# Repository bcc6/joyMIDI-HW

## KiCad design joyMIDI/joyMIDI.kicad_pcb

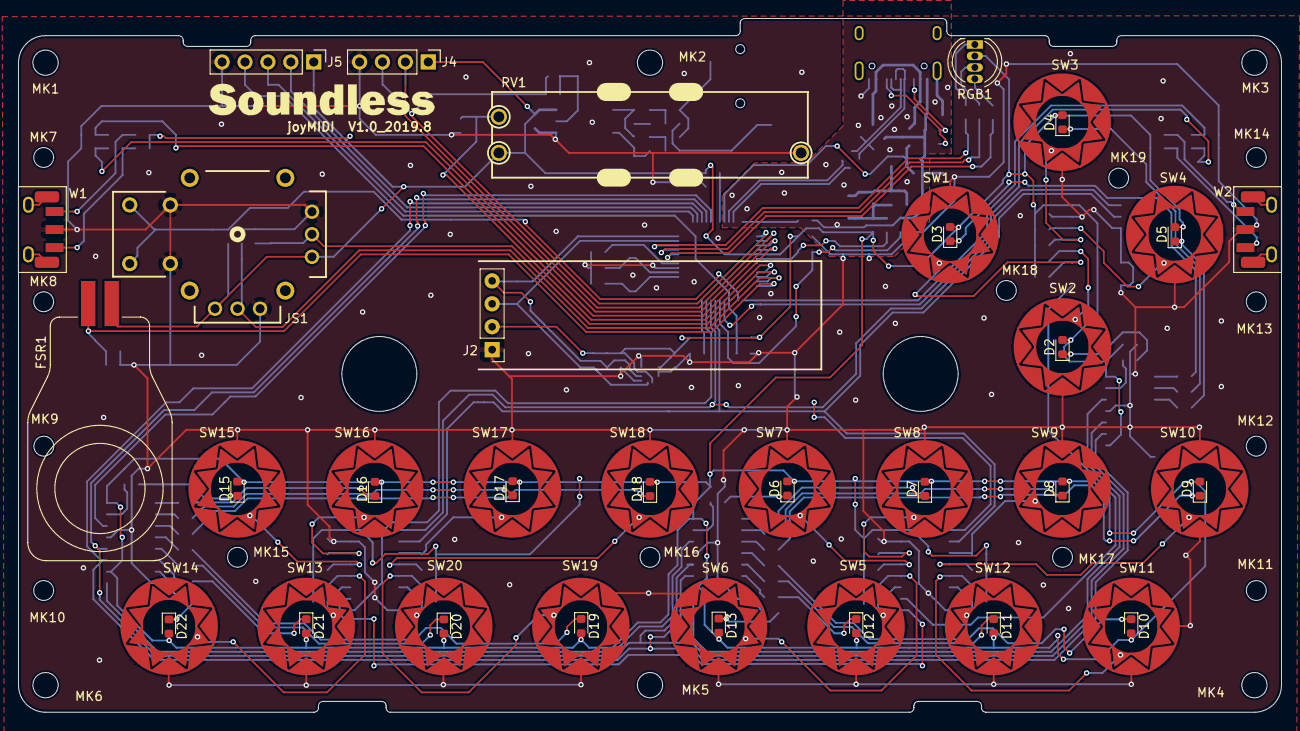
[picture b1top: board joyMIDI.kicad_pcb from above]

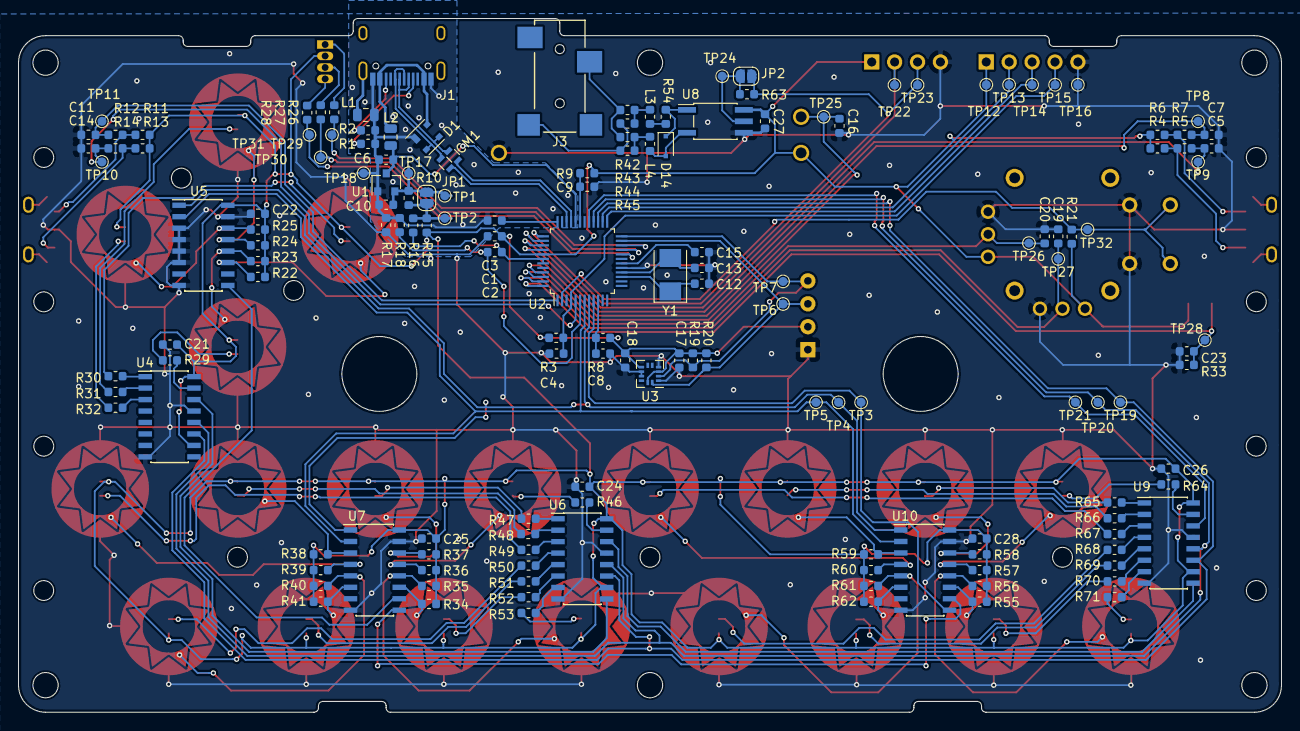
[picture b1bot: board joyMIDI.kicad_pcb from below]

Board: 2 copper layers, 140.0 x 76.9 mm, 221 parts (153 on the bottom side), 126 nets.

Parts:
C1, C2, C8, C9, C17, C18, C21, C22, C24, C25, C26, C27, C28: 100n; C_0603_1608Metric
C3, C4, C15: 1u; C_0603_1608Metric
C5, C7, C11, C14: 10n; C_0603_1608Metric
C6, C10: 4.7u; C_0603_1608Metric
C12, C13: 20p; C_0603_1608Metric
C16, C19, C20, C23: 1n; C_0603_1608Metric
CM1: 90R@100MHz; CommonChoke_Dual0603
D1: PRTR5V0U2X; PRTR5V0U2X_SOT-143B
D2, D3, D4, D5, D6, D7, D8, D9, D10, D11, D12, D13, D15, D16, D17, D18, D19, D20, D21, D22: LED; LED_0603_1608Metric
D14: 1N4148WS; D_SOD-323F
FSR1: GD10-20N; FSR_GD10-20N
J1: USB_Type_C_16P; HRO_TYPE-C-31-M-12
J2: HDR_01X04; Pin_Header_Straight_1x04_Pitch2.54mm_SmallHole
J3: AUDIO_JACK_TRS_4P_2.5mm; AUDIO_JACK_2.5mm_SJ-2524-SMT
J4: HDR_01X04; PinHeader_1x04_P2.54mm_Vertical
J5: HDR_01X05; PinHeader_1x05_P2.54mm_Vertical
JP1, JP2: SolderJumper; SolderJumper-2_P1.3mm_Open_RoundedPad1.0x1.5mm
JS1: Joystick; Joystick_FJM10K-S
L1: L0805/NC; L_0805_2012Metric
L2: L0805/600R_1A; L_0805_2012Metric
L3, L4: MMZ1608Y102BT; L_0603_1608Metric
MK1, MK2, MK3, MK4, MK5, MK6: NPTH_M2.6; NPTH_2.8mm_M2.6
MK7, MK8, MK9, MK10, MK11, MK12, MK13, MK14, MK15, MK16, MK17, MK18, MK19: NPTH_M2; NPTH_2.2mm_M2
R1, R2: 5.1K; R_0603_1608Metric
R3, R4, R5, R6, R7, R11, R12, R13, R14, R21, R22, R23, R24, R25, R34, R35, R36, R37, R38, R39, R40, R41, R55, R56, R57, R58, R59, R60, R61, R62: 10K; R_0603_1608Metric
R8, R9, R10, R15, R16, R17, R18, R42, R45, R63: 0R; R_0603_1608Metric
R19, R20: 4.7K; R_0603_1608Metric
R26, R27, R28, R54: 220; R_0603_1608Metric
R29, R30, R31, R32, R46, R47, R48, R49, R50, R51, R52, R53, R64, R65, R66, R67, R68, R69, R70, R71: 1K; R_0603_1608Metric
R33: 3.3K; R_0603_1608Metric
R43, R44: NC; R_0603_1608Metric
RGB1: LED_RGB_CA; LED_D4.8mm-4
RV1: VR_Slide; VR_Slide_F2031-NN
SW1, SW2, SW3, SW4, SW5, SW6, SW7, SW8, SW9, SW10, SW11, SW12, SW13, SW14, SW15, SW16, SW17, SW18, SW19, SW20: SW; RubberPad
TP1, TP2, TP3, TP4, TP5, TP6, TP7, TP8, TP9, TP10, TP11, TP12, TP13, TP14, TP15, TP16, TP17, TP18, TP19, TP20, TP21, TP22, TP23, TP24, TP25, TP26, TP27, TP28, TP29, TP30, TP31, TP32: TestPoint; TestPoint_Pad_D1.0mm
U1: AIC1746-33; SOT-23
U2: M452LE6AE; LQFP-48_7x7mm_P0.5mm
U3: BMA2xx; BMA2xx_LGA-12
U4, U6, U9: 74HC595; SOIC-16_3.9x9.9mm_P1.27mm
U5, U7, U10: 74HC165; SOIC-16_3.9x9.9mm_P1.27mm
U8: TLP2361; SO-5_4.4x3.6mm_P1.27mm
W1, W2: EC05E; EC05E1220202
Y1: 12M; Crystal_SMD_5032-2Pin_5.0x3.2mm

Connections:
/ADC1: C16.1, RV1.2, TP25.1, U2.45
/ADC2: C20.1, JS1.5, TP26.1, U2.46
/ADC3: C19.1, JS1.2, TP27.1, U2.47
/ADC4: C23.1, FSR1.1, R33.2, TP28.1, U2.48
/CURRENT_B: JP1.2, R10.1, R15.2, R16.2, TP2.1
/D+: CM1.4, D1.2, J1.A6, J1.B6
/D-: CM1.1, D1.3, J1.A7, J1.B7
/I2C_SCL: J2.3, R20.2, TP6.1, U2.23, U3.12
/I2C_SDA: J2.4, R19.2, TP7.1, U2.24, U3.2
/ICECLK: J5.3, TP14.1, U2.25
/ICEDAT: J5.2, TP13.1, U2.26
/JOG_1A: C7.1, R7.1, TP8.1, U2.40
/JOG_1B: C5.1, R5.1, TP9.1, U2.39
/JOG_2A: C14.1, R14.1, TP10.1, U2.5
/JOG_2B: C11.1, R12.1, TP11.1, U2.1
/KEY_CK: TP5.1, U2.7, U5.2, U7.2, U10.2
/KEY_ISP: JS1.7, R21.1, TP32.1, U2.2
/KEY_PL: TP4.1, U2.8, U5.1, U7.1, U10.1
/KEY_SI: TP3.1, U2.9, U10.9
/LED_B: R28.2, TP31.1, U2.20
/LED_DATA: TP21.1, U2.29, U9.14
/LED_G: R27.2, TP30.1, U2.21
/LED_R: R26.2, TP29.1, U2.22
/LED_RCLK: TP20.1, U2.28, U4.12, U6.12, U9.12
/LED_SRCLK: TP19.1, U2.27, U4.11, U6.11, U9.11
/MIDI_IN: JP2.1, R63.1, TP24.1, U8.5
/UART_RX: J4.3, JP2.2, R63.2, TP23.1, U2.37
/UART_TX: J4.2, TP22.1, U2.38
/VBAT: C8.1, R8.2, U2.10
/VDDIO: C9.1, R9.1, U2.31
/nRST: C4.1, J5.4, R3.2, TP15.1, U2.4
GND_ANA: C2.2, R18.1, U2.6
GND_DIG: C1.2, C4.2, C5.2, C7.2, C8.2, C9.2, C11.2, C12.2, C13.2, C14.2, C15.2, C16.2, C17.2, C18.2, C19.2, C20.2, C21.2, C22.1, C23.2, C24.2, C25.1, C26.2, C27.1, C28.1, J2.1, J4.4, J5.5, JS1.3, JS1.6, JS1.8, R17.1, R33.1, RV1.3, SW1.1, SW2.1, SW3.1, SW4.1, SW5.1, SW6.1, SW7.1, SW8.1, SW9.1, SW10.1, SW11.1, SW12.1, SW13.1, SW14.1, SW15.1, SW16.1, SW17.1, SW18.1, SW19.1, SW20.1, TP16.1, U2.17, U3.1, U3.4, U3.8, U3.9, U4.8, U4.13, U5.3, U5.4, U5.5, U5.6, U5.8, U5.15, U6.8, U6.13, U7.8, U7.15, U8.4, U9.8, U9.13, U10.8, U10.15, W1.3, W2.3
GND_PWR: C3.1, C6.2, C10.2, D1.1, J1.A1B12, J1.B1A12, L1.1, R1.1, R2.1, R17.2, R18.2, TP18.1, U1.1
unnamed: C3.2, U2.36
unnamed: C6.1, L2.1, U1.3, U2.32
unnamed: C12.1, U2.15, Y1.1
unnamed: C13.1, U2.16, Y1.2
unnamed: C15.1, U2.18
unnamed: CM1.2, U2.33
unnamed: CM1.3, U2.34
unnamed: D2.1, R29.2
unnamed: D3.1, R30.2
unnamed: D4.1, R31.2
unnamed: D5.1, R32.2
unnamed: D6.1, R46.2
unnamed: D7.1, R47.2
unnamed: D8.1, R48.2
unnamed: D9.1, R49.2
unnamed: D10.1, R50.2
unnamed: D11.1, R51.2
unnamed: D12.1, R52.2
unnamed: D13.1, R53.2
unnamed: D14.1, R54.2, U8.1
unnamed: D14.2, L4.2, U8.3
unnamed: D15.1, R64.2
unnamed: D16.1, R65.2
unnamed: D17.1, R66.2
unnamed: D18.1, R67.2
unnamed: D19.1, R68.2
unnamed: D20.1, R69.2
unnamed: D21.1, R70.2
unnamed: D22.1, R71.2
unnamed: J1.A5, R1.2
unnamed: J1.B5, R2.2
unnamed: J1.SH, L1.2
unnamed: J3.2, R43.1, R45.1
unnamed: J3.3, R42.1, R44.1
unnamed: L3.1, R42.2, R43.2
unnamed: L3.2, R54.1
unnamed: L4.1, R44.2, R45.2
unnamed: R4.1, R5.2, W1.2
unnamed: R6.1, R7.2, W1.1
unnamed: R11.1, R12.2, W2.2
unnamed: R13.1, R14.2, W2.1
unnamed: R22.1, SW1.2, U5.11
unnamed: R23.1, SW2.2, U5.12
unnamed: R24.1, SW3.2, U5.13
unnamed: R25.1, SW4.2, U5.14
unnamed: R26.1, RGB1.1
unnamed: R27.1, RGB1.3
unnamed: R28.1, RGB1.4
unnamed: R29.1, U4.15
unnamed: R30.1, U4.1
unnamed: R31.1, U4.2
unnamed: R32.1, U4.3
unnamed: R34.1, SW5.2, U7.11
unnamed: R35.1, SW6.2, U7.12
unnamed: R36.1, SW7.2, U7.13
unnamed: R37.1, SW8.2, U7.14
unnamed: R38.1, SW9.2, U7.3
unnamed: R39.1, SW10.2, U7.4
unnamed: R40.1, SW11.2, U7.5
unnamed: R41.1, SW12.2, U7.6
unnamed: R46.1, U6.15
unnamed: R47.1, U6.1
unnamed: R48.1, U6.2
unnamed: R49.1, U6.3
unnamed: R50.1, U6.4
unnamed: R51.1, U6.5
unnamed: R52.1, U6.6
unnamed: R53.1, U6.7
unnamed: R55.1, SW13.2, U10.11
unnamed: R56.1, SW14.2, U10.12
unnamed: R57.1, SW15.2, U10.13
unnamed: R58.1, SW16.2, U10.14
unnamed: R59.1, SW17.2, U10.3
unnamed: R60.1, SW18.2, U10.4
unnamed: R61.1, SW19.2, U10.5
unnamed: R62.1, SW20.2, U10.6
unnamed: R64.1, U9.15
unnamed: R65.1, U9.1
unnamed: R66.1, U9.2
unnamed: R67.1, U9.3
unnamed: R68.1, U9.4
unnamed: R69.1, U9.5
unnamed: R70.1, U9.6
unnamed: R71.1, U9.7
unnamed: U4.14, U6.9
unnamed: U5.9, U7.10
unnamed: U6.14, U9.9
unnamed: U7.9, U10.10
VBUS: D1.4, J1.A4B9, J1.B4A9, L2.2
VCC_ANA: C2.1, R16.1, U2.42, U2.43
VCC_DIG: C1.1, C17.1, C18.1, C21.1, C22.2, C24.1, C25.2, C26.1, C27.2, C28.2, D2.2, D3.2, D4.2, D5.2, D6.2, D7.2, D8.2, D9.2, D10.2, D11.2, D12.2, D13.2, D15.2, D16.2, D17.2, D18.2, D19.2, D20.2, D21.2, D22.2, FSR1.2, J2.2, J4.1, J5.1, JS1.1, JS1.4, R3.1, R4.2, R6.2, R8.1, R9.2, R11.2, R13.2, R15.1, R19.1, R20.1, R21.2, R22.2, R23.2, R24.2, R25.2, R34.2, R35.2, R36.2, R37.2, R38.2, R39.2, R40.2, R41.2, R55.2, R56.2, R57.2, R58.2, R59.2, R60.2, R61.2, R62.2, RGB1.2, RV1.1, TP12.1, U2.41, U3.3, U3.7, U3.11, U4.10, U4.16, U5.16, U6.10, U6.16, U7.16, U8.6, U9.10, U9.16, U10.16
VCC_PWR: C10.1, JP1.1, R10.2, TP1.1, TP17.1, U1.2

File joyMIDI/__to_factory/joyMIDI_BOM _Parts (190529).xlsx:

| No. | Reference | P/N | Value | Package | Quantity | Mount
 | 1 | C1, C2, C8, C9, C17, C18, C21, C22, C24, C25, C26, C27, C28 |  | 100n | C0603 | 13 | Yes
 | 2 | C12, C13 |  | 20p | C0603 | 2 | Yes
 | 3 | C16, C19, C20, C23 |  | 1n | C0603 | 4 | Yes
 | 4 | C3, C4, C15 |  | 1u | C0603 | 3 | Yes
 | 5 | C5, C7, C11, C14 |  | 10n | C0603 | 4 | Yes
 | 6 | C6, C10 |  | 4.7u, 10V | C0603 | 2 | Yes
 | 7 | CM1 | TDK, ACM2012-900-2P-TL002 | Common Choke, 90R@100MHz |  | 1 | Yes(0R)
 | 8 | D1 | Nexperia, PRTR5V0U2X | ESD protection | SOT-143B | 1 | No
 | 9 | D14 | 1N4148WS | Diode | SOD-323F | 1 | Yes
 | 10 | D2, D3, D4, D5, D6, D7, D8, D9, D10, D11, D12, D13, D15, D16, D17, D18, D19, D2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 | Everlight, 19-217/W1D | LED, Pure White | LED0603 | 20 | Yes
 | 11 | FSR1 | Uneo, GD10-20N | Forcing sensing resister |  | 1 | Yes | http://www.uneotech.com/uneo/us/online-store-4/96/gs0001-4-u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 Eric Huang…
 | 12 | J1 | Amphenol, 12401610E4#2A | USB Type C, Receptacle |  | 1 | Yes
 | 13 | J2 |  | Pin Header (OLED) | 1x4_2.54mm | 1 | Yes
 | 14 | J3 | CUI, SJ-2524-SMT | Audio Jack, 2.5mm |  | 1 | Yes
 | 15 | J4 |  | Pin Header (Debug) | 1x4_2.54mm | 1 | No
 | 16 | J5 |  | Pin Header (Programmer) | 1x5_2.54mm | 1 | No
 | 17 | JS1 | 普耀(福哥), FJM10K-S1B10K | Joystick |  | 1 | Yes | http://www.polyshine.cn/uploadFile/FJM10K-2013-12-02-04-50-09.pdf
 | 18 | L1 |  | 0R | L0805 | 1 | No
 | 19 | L2 |  | Ferrite Bead, 600R, 1A | L0805 | 1 | Yes (0R)
 | 20 | L3, L4 | TDK, MMZ1608Y102BT | Ferrite Bead | L0603 | 2 | Yes (0R)
 | 21 | R1, R2 |  | 5.1K | R0603 | 2 | Yes
 | 22 | R19, R20 |  | 4.7K | R0603 | 2 | Yes
 | 23 | R26, R27, R28, R54 |  | 220 | R0603 | 4 | Yes
 | 24 | R29, R30, R31, R32, R46, R47, R48, R49, R50, R51, R52, R53, R64, R65, R66, R67,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 |  | 1K | R0603 | 20 | Yes
 | 25 | R3, R4, R5, R6, R7, R11, R12, R13, R14, R21, R22, R23, R24, R25, R34, R35, R36,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 |  | 10K | R0603 | 30 | Yes
 | 26 | R33 |  | 2K | R0603 | 1 | Yes
 | 27 | R43, R44 |  | NC | R0603 | 2 | No
 | 28 | R8, R9, R10, R15, R16, R17, R18, R42, R45, R63 |  | 0R | R0603 | 10 | Yes
 | 29 | RV1 | 普耀(福哥), F2031-NN0SC2B10K | Slider, Travel 20mm, 3Pin 10KOhm | (操作力度為最鬆) | 1 | Yes | http://www.polyshine.cn/uploadFile/Fxx31-2015-09-21-01-46-32.pdf
 | 30 | RGB1 |  | LED, RGB Clear Common Anode | D4.8mm-4pin, Straw hat | 1 | Yes | https://detail.1688.com/offer/1232851898.html?spm=a2615.7691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
 | 31 | U1 | AIC, AIC1746-33(GU3TR, PK3TR) | LDO, 3.3V | SOT-23 | 1 | Yes
 | 32 | U2 | Nuvoton, M452LE6AE | MCU, 128K/32K | LQFP-48, 7x7mm | 1 | Yes
 | 33 | U3 | Bosch, BMA253 | G-sensor | LGA-12, 2x2mm | 1 | Yes | https://www.mouser.com/datasheet/2/783/Bosch_01242017_BMA253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
 | 34 | U4, U6, U9 | 74HC595D |  | SOIC-16, 3.9x9.9mm | 3 | Yes
 | 35 | U5, U7, U10 | 74HC165D |  | SOIC-16, 3.9x9.9mm | 3 | Yes
 | 36 | U8 | Toshiba, TLP2361 | Photocoupler | SO-5, 4.4x3.6mm | 1 | Yes
 | 37 | W1, W2 | ALPS, EC05E1220202 | Encoder |  | 2 | Yes | https://www.alps.com/prod/info/E/HTML/Encoder/Incremental/EC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
 | 38 | Y1 | TXC, 7A-12.000MAAJ-T | 12MHz, 20pf | SMD 5032, 2Pin | 1 | Yes
 | No. | Reference | P/N | Value | Package | Quantity | Mount
 | 1 | OLED |  | 128x32, White color, I2C | 0.91" | 1 | Yes | https://item.taobao.com/item.htm?spm=a1z09.2.0.0.46752e8dvI4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
 | 2 | Optical fiber |  | SOTT-4 | Φ 4mm (裁切長度為 55mm) | 1 | Yes | https://item.taobao.com/item.htm?spm=a312a.7700824.w4002-223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
 | 3 | Heat shrink tube |  |  | Φ 5mm (裁切長度為 16mm) | 1 | Yes
 | 4 | Joystick cap |  | Plastic |  | 1 | Yes | https://item.taobao.com/item.htm?spm=a1z09.2.0.0.46752e8dkIG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
 | 5 | Slider cap |  | Plastic |  | 1 | Yes | https://item.taobao.com/item.htm?spm=a230r.1.14.61.41f04349y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
 | 6 | PCB |  | Matte Black / White font

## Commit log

2019-05-27 V1.0 2019.5 Change USB connector to 16pin from 24pin Add placement file for SMT
2019-05-27 Fixed something
2019-05-28 Update gerber
2019-05-29 Update ibom plugin
2019-05-29 Update modules
2019-05-29 Add fabrication files
2019-08-20 Change Logo
